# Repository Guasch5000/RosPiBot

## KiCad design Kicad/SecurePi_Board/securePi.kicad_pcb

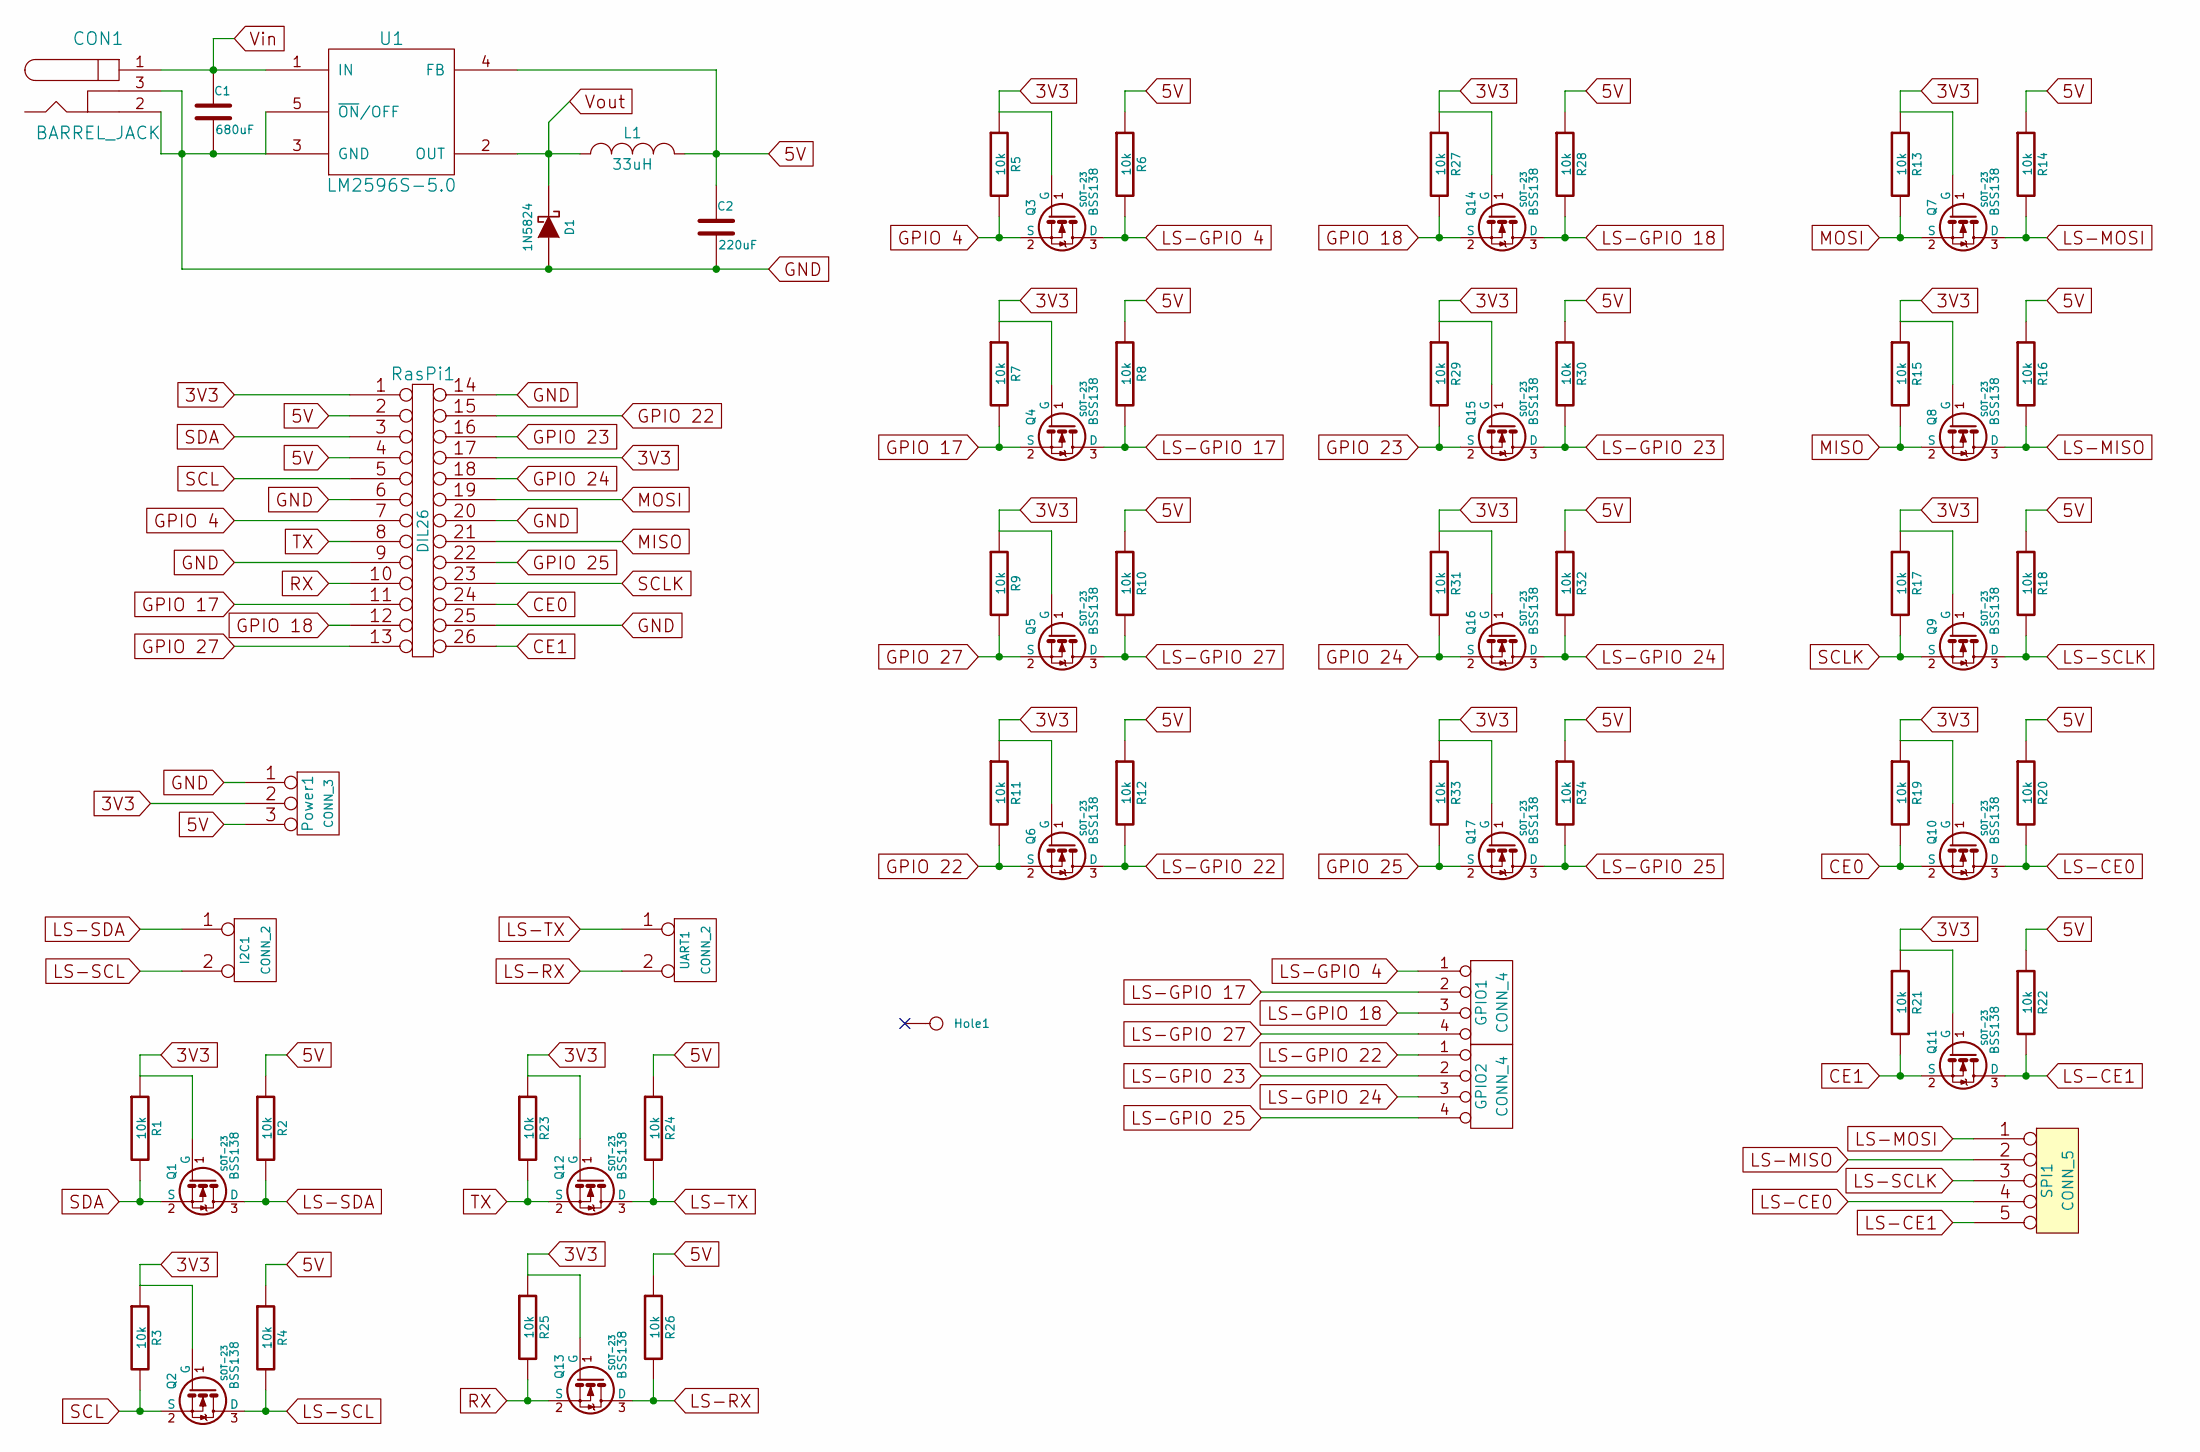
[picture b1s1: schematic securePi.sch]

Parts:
C1: 680uF
C2: 220uF
CON1: BARREL_JACK
D1: 1N5824
GPIO1, GPIO2: CONN_4
Hole1: CONN_1
I2C1: CONN_2
L1: 33uH
Power1: CONN_3
Q1, Q2, Q3, Q4, Q5, Q6, Q7, Q8, Q9, Q10, Q11, Q12, Q13, Q14, Q15, Q16, Q17: BSS138; SOT-23
R1, R2, R3, R4, R5, R6, R7, R8, R9, R10, R11, R12, R13, R14, R15, R16, R17, R18, R19, R20, R21, R22, R23, R24, R25, R26, R27, R28, R29, R30, R31, R32, R33, R34: 10k
RasPi1: DIL26
SPI1: CONN_5
U1: LM2596S-5.0
UART1: CONN_2

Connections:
3V3: Power1.2 (PM), Q1.1 (G), Q2.1 (G), Q3.1 (G), Q4.1 (G), Q5.1 (G), Q6.1 (G), Q7.1 (G), Q8.1 (G), Q9.1 (G), Q10.1 (G), Q11.1 (G), Q12.1 (G), Q13.1 (G), Q14.1 (G), Q15.1 (G), Q16.1 (G), Q17.1 (G), R1.1, R3.1, R5.1, R7.1, R9.1, R11.1, R13.1, R15.1, R17.1, R19.1, R21.1, R23.1, R25.1, R27.1, R29.1, R31.1, R33.1, RasPi1.1, RasPi1.17
5V: C2.1, L1.2, Power1.3, R2.1, R4.1, R6.1, R8.1, R10.1, R12.1, R14.1, R16.1, R18.1, R20.1, R22.1, R24.1, R26.1, R28.1, R30.1, R32.1, R34.1, RasPi1.2, RasPi1.4, U1.4 (FB)
CE0: Q10.2 (S), R19.2, RasPi1.24
CE1: Q11.2 (S), R21.2, RasPi1.26
GND: C1.2, C2.2, CON1.2, CON1.3, D1.1 (A), Power1.1, RasPi1.6, RasPi1.9, RasPi1.14, RasPi1.20, RasPi1.25, U1.3 (GND), U1.5 (~ON~/OFF)
GPIO 4: Q3.2 (S), R5.2, RasPi1.7
GPIO 17: Q4.2 (S), R7.2, RasPi1.11
GPIO 18: Q14.2 (S), R27.2, RasPi1.12
GPIO 22: Q6.2 (S), R11.2, RasPi1.15
GPIO 23: Q15.2 (S), R29.2, RasPi1.16
GPIO 24: Q16.2 (S), R31.2, RasPi1.18
GPIO 25: Q17.2 (S), R33.2, RasPi1.22
GPIO 27: Q5.2 (S), R9.2, RasPi1.13
LS-CE0: Q10.3 (D), R20.2, SPI1.4
LS-CE1: Q11.3 (D), R22.2, SPI1.5
LS-GPIO 4: GPIO1.1, Q3.3 (D), R6.2
LS-GPIO 17: GPIO1.2, Q4.3 (D), R8.2
LS-GPIO 18: GPIO1.3, Q14.3 (D), R28.2
LS-GPIO 22: GPIO2.1, Q6.3 (D), R12.2
LS-GPIO 23: GPIO2.2, Q15.3 (D), R30.2
LS-GPIO 24: GPIO2.3, Q16.3 (D), R32.2
LS-GPIO 25: GPIO2.4, Q17.3 (D), R34.2
LS-GPIO 27: GPIO1.4, Q5.3 (D), R10.2
LS-MISO: Q8.3 (D), R16.2, SPI1.2
LS-MOSI: Q7.3 (D), R14.2, SPI1.1
LS-RX: Q13.3 (D), R26.2, UART1.2 (PM)
LS-SCL: I2C1.2 (PM), Q2.3 (D), R4.2
LS-SCLK: Q9.3 (D), R18.2, SPI1.3
LS-SDA: I2C1.1, Q1.3 (D), R2.2
LS-TX: Q12.3 (D), R24.2, UART1.1
MISO: Q8.2 (S), R15.2, RasPi1.21
MOSI: Q7.2 (S), R13.2, RasPi1.19
RX: Q13.2 (S), R25.2, RasPi1.10
SCL: Q2.2 (S), R3.2, RasPi1.5
SCLK: Q9.2 (S), R17.2, RasPi1.23
SDA: Q1.2 (S), R1.2, RasPi1.3
TX: Q12.2 (S), R23.2, RasPi1.8
Vin: C1.1, CON1.1, U1.1 (IN)
Vout: D1.2 (K), L1.1, U1.2 (OUT)

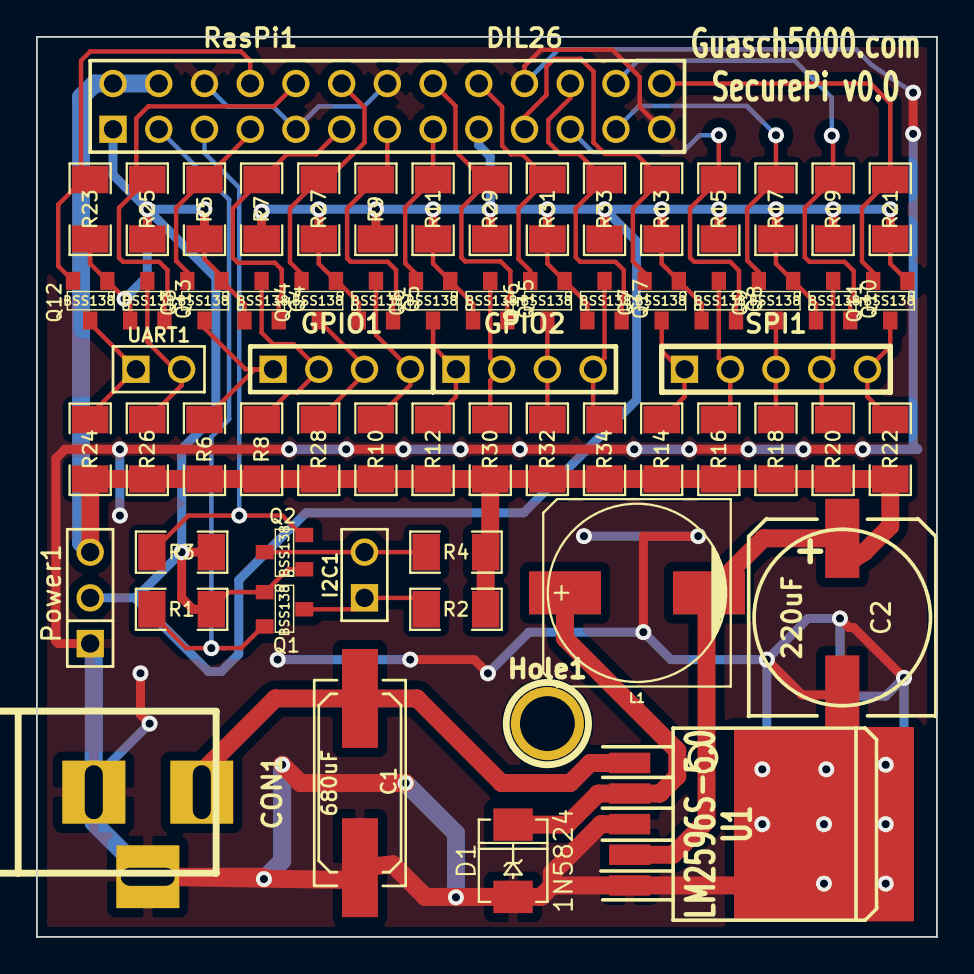
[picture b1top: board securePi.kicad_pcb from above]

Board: 2 copper layers, 50.0 x 50.0 mm, 65 parts (0 on the bottom side), 39 nets.

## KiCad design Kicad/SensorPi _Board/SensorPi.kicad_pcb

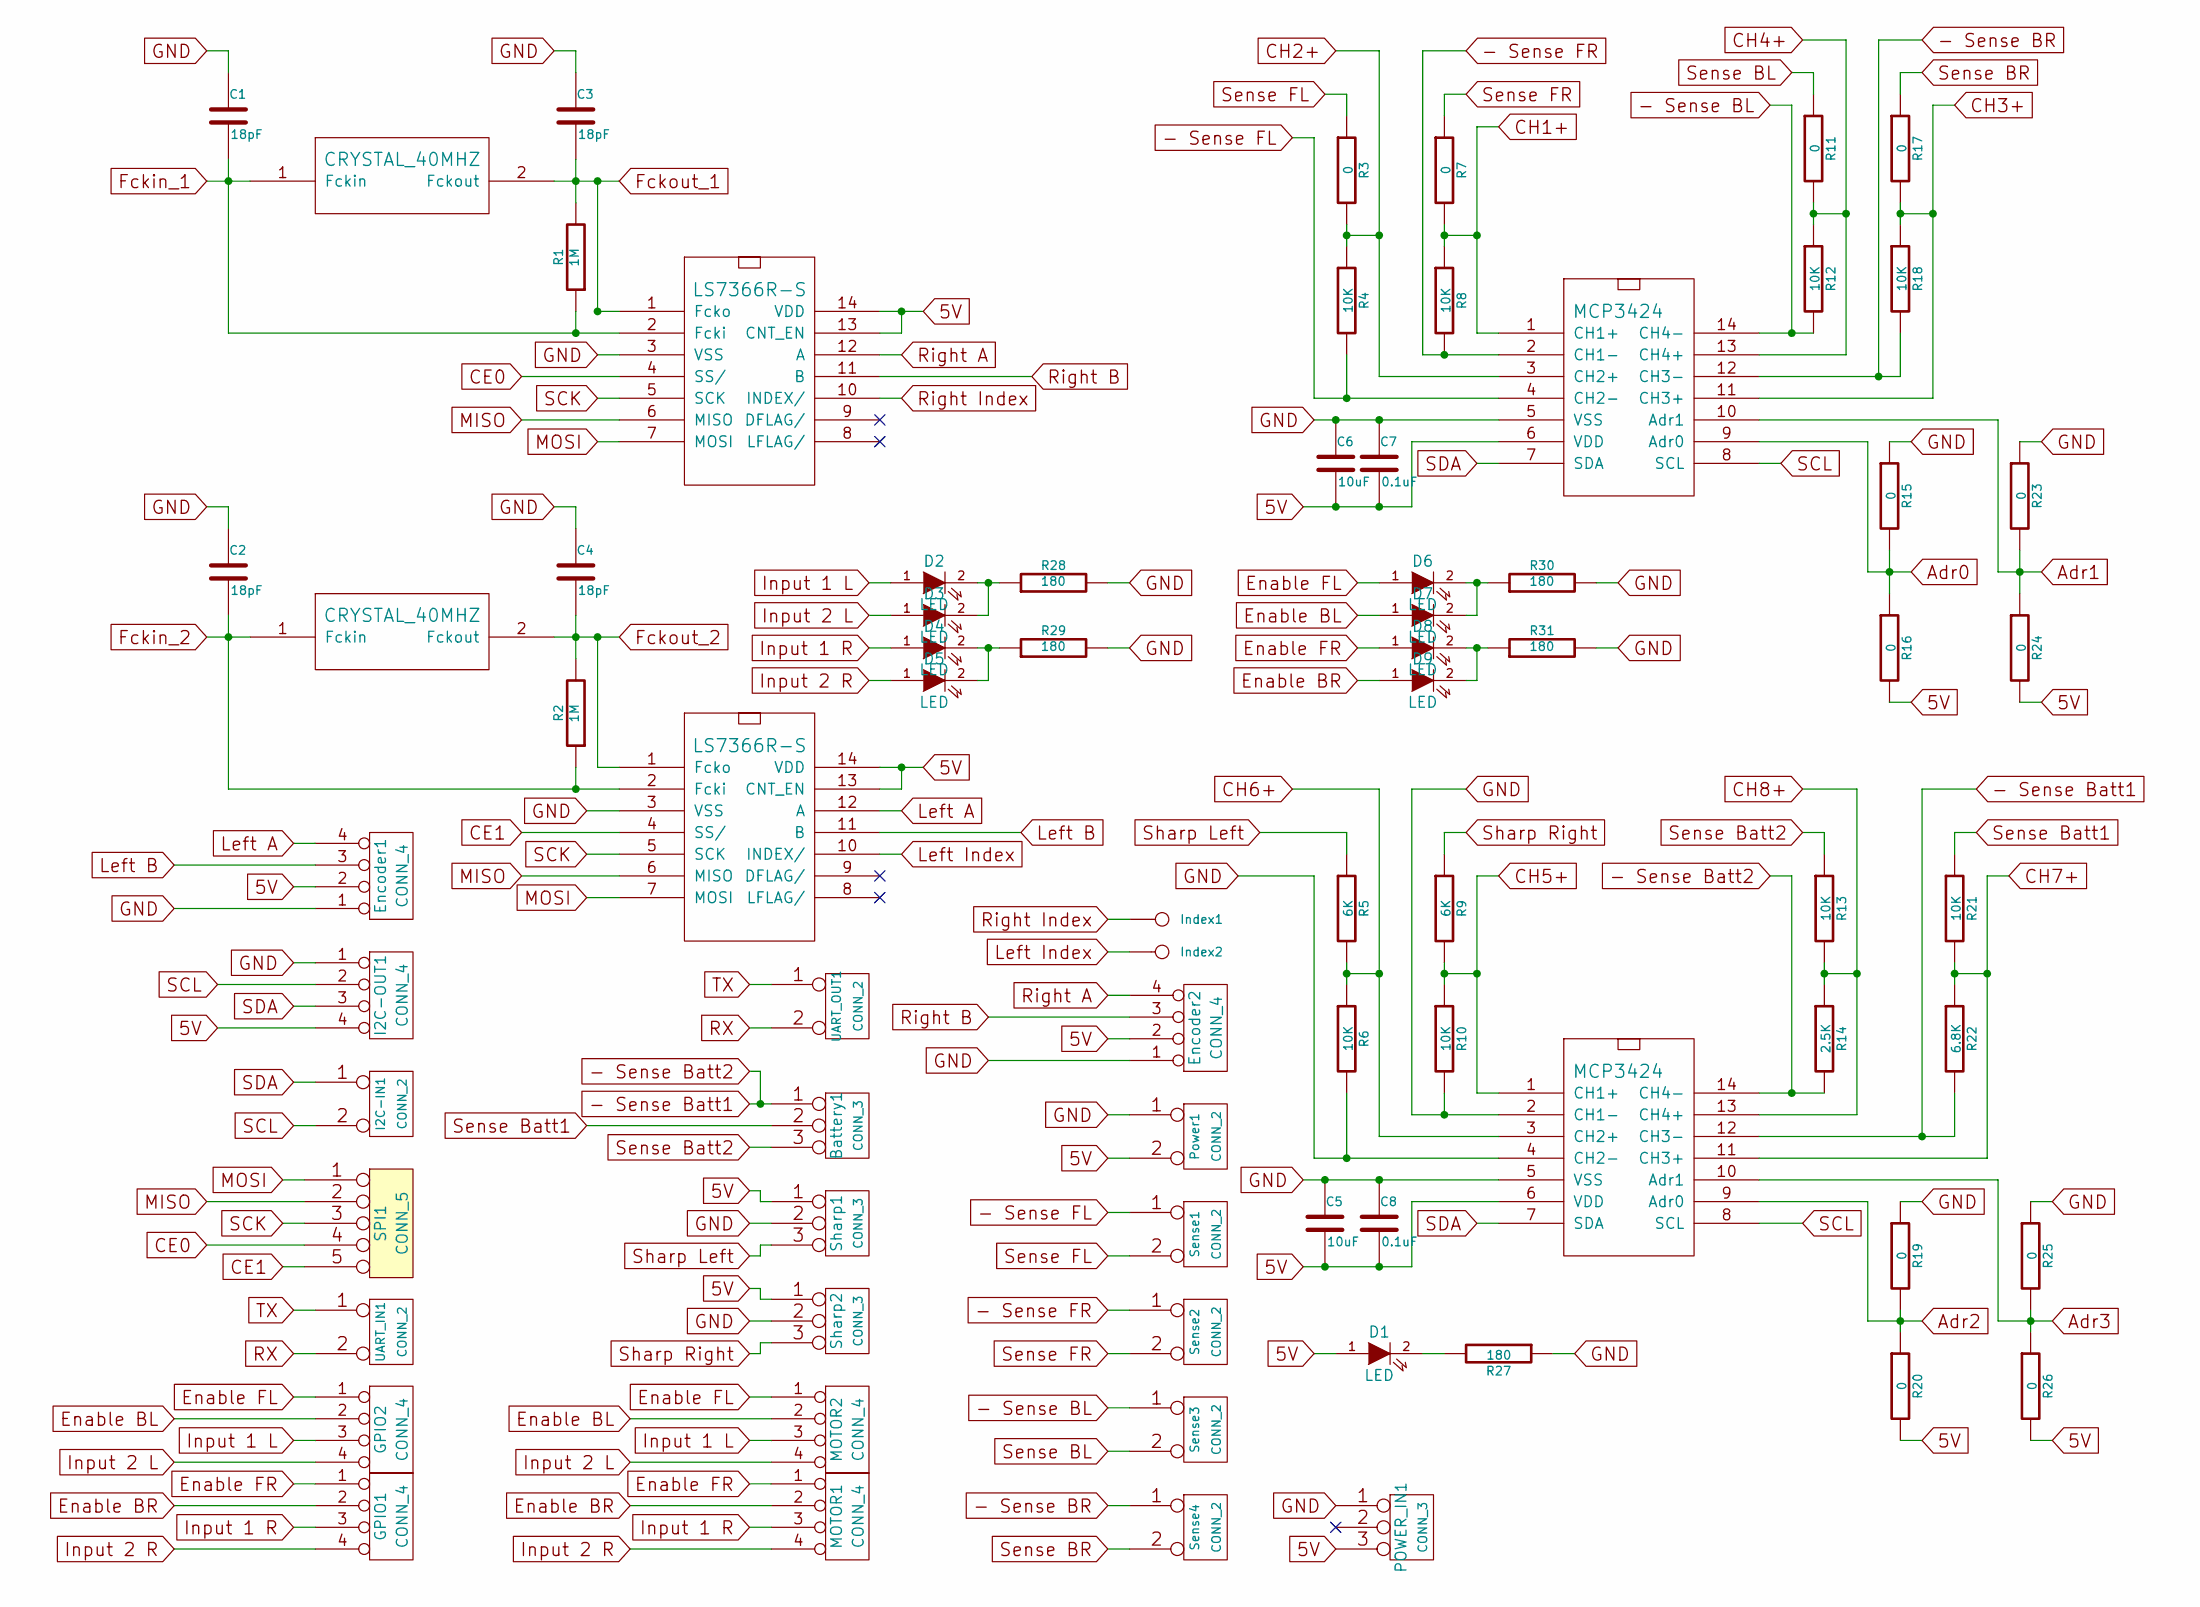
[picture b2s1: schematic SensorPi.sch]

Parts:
Battery1: CONN_3
C1, C2, C3, C4: 18pF
C5, C6: 10uF
C7, C8: 0.1uF
D1, D2, D3, D4, D5, D6, D7, D8, D9: LED
Encoder1, Encoder2: CONN_4
GPIO1, GPIO2: CONN_4
I2C-IN1: CONN_2
I2C-OUT1: CONN_4
Index1, Index2: CONN_1
MOTOR1, MOTOR2: CONN_4
POWER_IN1: CONN_3
Power1: CONN_2
R1, R2: 1M
R3, R7, R11, R15, R16, R17, R19, R20, R23, R24, R25, R26: 0
R4, R6, R8, R10, R12, R13, R18, R21: 10K
R5, R9: 6K
R14: 2.5K
R22: 6.8K
R27, R28, R29, R30, R31: 180
SMD1, SMD2: CRYSTAL_40MHZ
SOIC1, SOIC2: LS7366R-S
SOIC_1, SOIC_2: MCP3424
SPI1: CONN_5
Sense1, Sense2, Sense3, Sense4: CONN_2
Sharp1, Sharp2: CONN_3
UART_IN1: CONN_2
UART_OUT1: CONN_2

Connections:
5V: C5.2, C6.2, C7.2, C8.2, D1.1 (A), Encoder1.2, Encoder2.2, I2C-OUT1.4, POWER_IN1.3, Power1.2 (PM), R16.2, R20.2, R24.2, R26.2, SOIC1.13 (CNT_EN), SOIC1.14 (VDD), SOIC2.13 (CNT_EN), SOIC2.14 (VDD), SOIC_1.6 (VDD), SOIC_2.6 (VDD), Sharp1.1, Sharp2.1; also elsewhere on the board
- Sense BL: R12.2, SOIC_1.14 (CH4-), Sense3.1
- Sense BR: R18.2, SOIC_1.12 (CH3-), Sense4.1
- Sense Batt1: Battery1.1, R14.2, R22.2, SOIC_2.12 (CH3-), SOIC_2.14 (CH4-)
- Sense FL: R4.2, SOIC_1.4 (CH2-), Sense1.1
- Sense FR: R8.2, SOIC_1.2 (CH1-), Sense2.1
Adr0: R15.2, R16.1, SOIC_1.9 (Adr0)
Adr1: R23.2, R24.1, SOIC_1.10 (Adr1)
Adr2: R19.2, R20.1, SOIC_2.9 (Adr0)
Adr3: R25.2, R26.1, SOIC_2.10 (Adr1)
CE0: SOIC1.4 (SS/), SPI1.4
CE1: SOIC2.4 (SS/), SPI1.5
CH1+: R7.2, R8.1, SOIC_1.1 (CH1+)
CH2+: R3.2, R4.1, SOIC_1.3 (CH2+)
CH3+: R17.2, R18.1, SOIC_1.11 (CH3+)
CH4+: R11.2, R12.1, SOIC_1.13 (CH4+)
CH5+: R9.2, R10.1, SOIC_2.1 (CH1+)
CH6+: R5.2, R6.1, SOIC_2.3 (CH2+)
CH7+: R21.2, R22.1, SOIC_2.11 (CH3+)
CH8+: R13.2, R14.1, SOIC_2.13 (CH4+)
Enable BL: D7.1 (A), GPIO2.2, MOTOR2.2
Enable BR: D9.1 (A), GPIO1.2, MOTOR1.2
Enable FL: D6.1 (A), GPIO2.1, MOTOR2.1
Enable FR: D8.1 (A), GPIO1.1, MOTOR1.1
Fckin_1: C1.2, R1.1, SMD1.1 (Fckin), SOIC1.2 (Fcki)
Fckin_2: C2.2, R2.1, SMD2.1 (Fckin), SOIC2.2 (Fcki)
Fckout_1: C3.2, R1.2, SMD1.2 (Fckout), SOIC1.1 (Fcko)
Fckout_2: C4.2, R2.2, SMD2.2 (Fckout), SOIC2.1 (Fcko)
GND: C1.1, C2.1, C3.1, C4.1, C5.1, C6.1, C7.1, C8.1, Encoder1.1, Encoder2.1, I2C-OUT1.1, POWER_IN1.1, Power1.1, R6.2, R10.2, R15.1, R19.1, R23.1, R25.1, R27.1, R28.2, R29.2, R30.2, R31.2, SOIC1.3 (VSS), SOIC2.3 (VSS), SOIC_1.5 (VSS), SOIC_2.2 (CH1-), SOIC_2.4 (CH2-), SOIC_2.5 (VSS), Sharp1.2 (PM), Sharp2.2 (PM); also elsewhere on the board
Input 1 L: D2.1 (A), GPIO2.3, MOTOR2.3
Input 1 R: D4.1 (A), GPIO1.3, MOTOR1.3
Input 2 L: D3.1 (A), GPIO2.4, MOTOR2.4
Input 2 R: D5.1 (A), GPIO1.4, MOTOR1.4
Left A: Encoder1.4, SOIC2.12 (A)
Left B: Encoder1.3, SOIC2.11 (B)
Left Index: Index2.1, SOIC2.10 (INDEX/)
MISO: SOIC1.6 (MISO), SOIC2.6 (MISO), SPI1.2
MOSI: SOIC1.7 (MOSI), SOIC2.7 (MOSI), SPI1.1
unnamed: D4.2 (K), D5.2 (K), R29.1
unnamed: D2.2 (K), D3.2 (K), R28.1
unnamed: D1.2 (K), R27.2
unnamed: D6.2 (K), D7.2 (K), R30.1
unnamed: D8.2 (K), D9.2 (K), R31.1
RX: UART_IN1.2 (PM), UART_OUT1.2 (PM); also elsewhere on the board
Right A: Encoder2.4, SOIC1.12 (A)
Right B: Encoder2.3, SOIC1.11 (B)
Right Index: Index1.1, SOIC1.10 (INDEX/)
SCK: SOIC1.5 (SCK), SOIC2.5 (SCK), SPI1.3
SCL: I2C-IN1.2 (PM), I2C-OUT1.2, SOIC_1.8 (SCL), SOIC_2.8 (SCL); also elsewhere on the board
SDA: I2C-IN1.1, I2C-OUT1.3, SOIC_1.7 (SDA), SOIC_2.7 (SDA); also elsewhere on the board
Sense BL: R11.1, Sense3.2 (PM)
Sense BR: R17.1, Sense4.2 (PM)
Sense Batt1: Battery1.2 (PM), R21.1
Sense Batt2: Battery1.3, R13.1
Sense FL: R3.1, Sense1.2 (PM)
Sense FR: R7.1, Sense2.2 (PM)
Sharp Left: R5.1, Sharp1.3
Sharp Right: R9.1, Sharp2.3
TX: UART_IN1.1, UART_OUT1.1; also elsewhere on the board

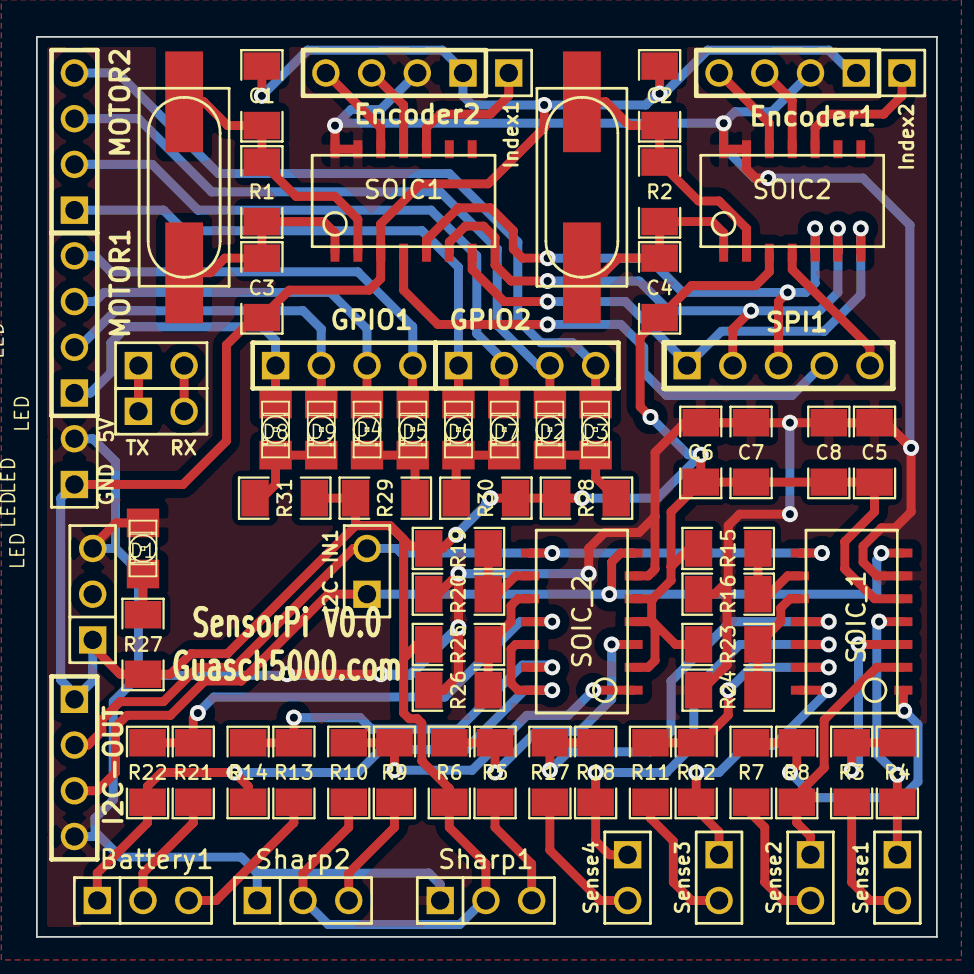
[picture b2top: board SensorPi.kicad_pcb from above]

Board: 2 copper layers, 50.0 x 50.0 mm, 76 parts (0 on the bottom side), 59 nets.

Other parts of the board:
GND  5V: CONN_2; PIN_ARRAY_2X1
I2C-OUT: CONN_4; PIN_ARRAY_4x1
TX  RX: CONN_2; PIN_ARRAY_2X1

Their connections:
5V: GND 5V.2, I2C-OUT.4; also elsewhere on the board
GND: GND 5V.1, I2C-OUT.1; also elsewhere on the board
RX: TX RX.2; also elsewhere on the board
SCL: I2C-OUT.2; also elsewhere on the board
SDA: I2C-OUT.3; also elsewhere on the board
TX: TX RX.1; also elsewhere on the board

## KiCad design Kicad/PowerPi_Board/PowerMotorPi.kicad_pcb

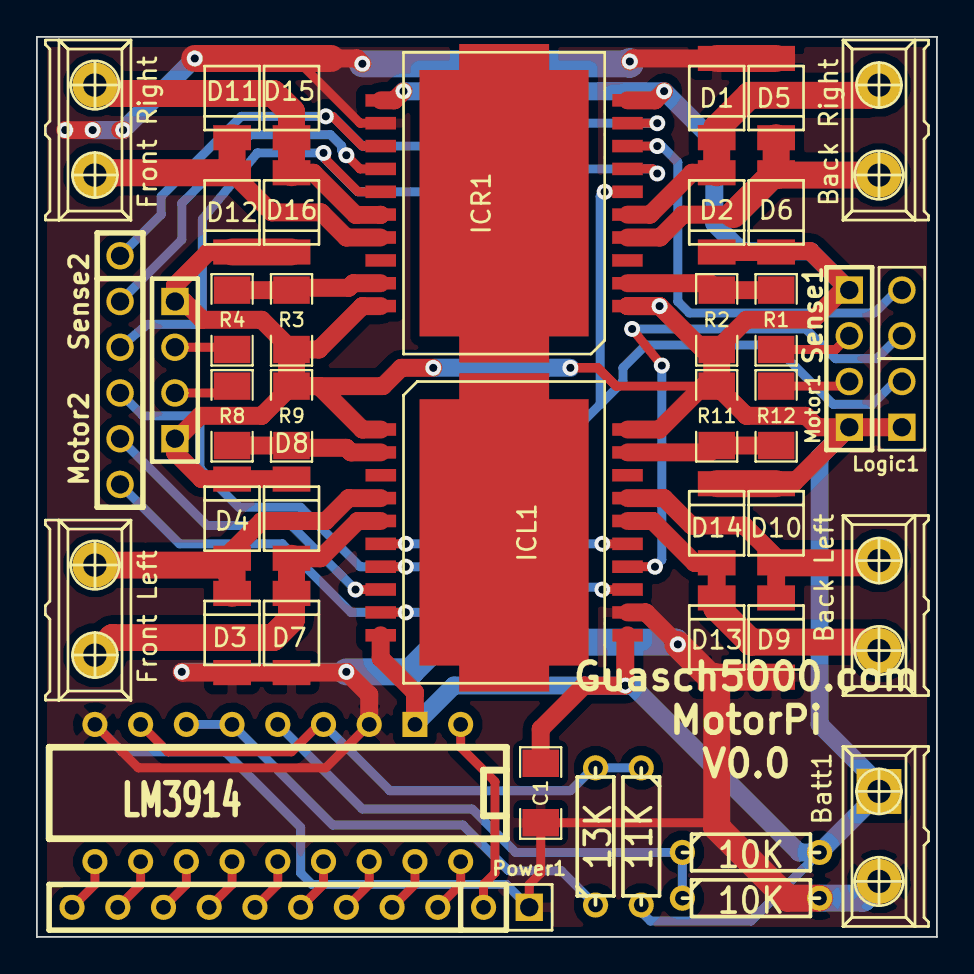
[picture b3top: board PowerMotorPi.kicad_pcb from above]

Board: 2 copper layers, 50.0 x 50.0 mm, 44 parts (0 on the bottom side), 40 nets.

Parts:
Back Left: CONN_2; Block_Terminal_green_2_pins
Back Right: CONN_2; Block_Terminal_green_2_pins
Batt1: CONN_2; Block_Terminal_green_2_pins_Batt
C1: 1uF; SM1206
D1, D2, D3, D4, D5, D6, D7, D8, D9, D10, D11, D12, D13, D14, D15, D16: DIODESCH; SMD_Schottky
DIP1: LM3914; DIP-18__300
Front Left: CONN_2; Block_Terminal_green_2_pins
Front Right: CONN_2; Block_Terminal_green_2_pins
ICL1: L298; L298P
ICR1: L298; L298P
LED1: CONN_10; SIL-10
Logic1: CONN_2; PIN_ARRAY_2X1
Motor1: CONN_2; PIN_ARRAY_2X1
Motor2: CONN_6; PIN_ARRAY-6X1
Power1: CONN_1; PIN_ARRAY_1
R1, R4, R8, R12: 1K; SM1206
R2, R3, R9, R11: 0.5; SM1206
R5, R6: 10K; R3
R7: 11K; R3
R10: 13K; R3
Sense1, Sense2: CONN_4; PIN_ARRAY_4x1

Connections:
5V: ICL1.6, ICR1.6, Logic1.2
GND: Batt1.1, C1.1, D2.1, D4.1, D6.1, D8.1, D10.1, D12.1, D14.1, D16.1, DIP1.2, ICL1.1, ICL1.10, ICL1.11, ICL1.20, ICR1.1, ICR1.10, ICR1.11, ICR1.20, Logic1.1, R2.2, R3.2, R6.2, R7.2, R9.2, R11.2, Sense1.1, Sense1.4, Sense2.1, Sense2.4
IN: DIP1.5, R5.1, R6.1
L Enable A: ICL1.8, Motor2.5
L Enable B: ICL1.14, Motor1.2
L Input 1: ICL1.7, ICL1.15, Motor2.4
L Input 2: ICL1.9, ICL1.13, Motor2.6
L Out 1: D3.1, D4.2, Front Left.2, ICL1.4
L Out 2: D7.1, D8.2, Front Left.1, ICL1.5
L Out 3: Back Left.2, D13.1, D14.2, ICL1.16
L Out 4: Back Left.1, D9.1, D10.2, ICL1.17
L Sense A: ICL1.2, R8.2, R9.1
L Sense ADC A: R8.1, Sense2.2
L Sense ADC B: R12.1, Sense1.3
L Sense B: ICL1.19, R11.1, R12.2
Led 1: DIP1.1, LED1.1
Led 2: DIP1.18, LED1.2
Led 3: DIP1.17, LED1.3
Led 4: DIP1.16, LED1.4
Led 5: DIP1.15, LED1.5
Led 6: DIP1.14, LED1.6
Led 7: DIP1.13, LED1.7
Led 8: DIP1.12, LED1.8
Led 9: DIP1.11, LED1.9
Led 10: DIP1.10, LED1.10
R Enable A: ICR1.8, Motor1.1
R Enable B: ICR1.14, Motor2.2
R Input 1: ICR1.7, ICR1.15, Motor2.3
R Input 2: ICR1.9, ICR1.13, Motor2.1
R Out 1: Back Right.2, D5.1, D6.2, ICR1.4
R Out 2: Back Right.1, D1.1, D2.2, ICR1.5
R Out 3: D15.1, D16.2, Front Right.2, ICR1.16
R Out 4: D11.1, D12.2, Front Right.1, ICR1.17
R Sense A: ICR1.2, R1.2, R2.1
R Sense ADC A: R1.1, Sense1.2
R Sense ADC B: R4.1, Sense2.3
R Sense B: ICR1.19, R3.1, R4.2
R_hi: DIP1.6, DIP1.7, R10.1
R_lo: DIP1.4, DIP1.8, R7.1, R10.2
VSS: Batt1.2, C1.2, D1.2, D3.2, D5.2, D7.2, D9.2, D11.2, D13.2, D15.2, DIP1.3, DIP1.9, ICL1.12, ICR1.12, Power1.1, R5.2

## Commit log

2014-03-10 including all kicad files
2014-03-10 adding folders
2014-03-12 adding LaTex files
2014-03-14 Creating LaTex template
2014-03-14 updating template
2014-03-14 Latex Especification write
2014-03-14 changing Informatica to Software concept
2014-03-14 updating latex
2014-03-17 adding I2C ultrasound sensor comunication
2014-03-18 adding reading with two devices
2014-03-21 web based terminal
2014-03-21 modify KS103 codes
2014-03-24 Changing name to the project
2014-03-24 More specification in latex document
2014-03-24 adding electronics and mechanics specifications
2014-03-24 modifing Specifications and Resume
2014-03-25 changing abstract text and adding Modification part
2014-03-27 Adding battery modifications
2014-03-31 losing time...
2014-04-01 Updating Raspberry Pi description
2014-04-01 Updating wifibot description
2014-04-01 time to coffe! enough Latex
2014-04-01 Quadrature Encoder explanation (after coffee)
2014-04-02 Updating battery decision
2014-04-08 Adding ADC module comunication via I2c
2014-04-30 more latex
2014-05-02 electronic components
2014-05-07 adding regulator descripction
2014-05-07 More Buck description
2014-05-10 Adding more modification in Latex
2014-05-12 More Latexz
2014-05-13 PCB definitions
2014-05-13 Adding MemCached examples
    Used for sahring variable between scripts in python. Also can be used
    for PHP
2014-05-17 Ading Wired connections Latex
2014-05-17 Changing Latex name file
2014-05-18 Adding Mechanical modification in Latex
2014-05-18 Finished assembly chapter
2014-05-18 Adding SolidWorks files
2014-05-18 Adding Data Publisher codes
2014-05-22 Adding Software description in Latex
2014-05-22 Module Description
2014-05-24 Basic programs descriptions, Publishers
2014-05-24 Finished rospibot module description
2014-05-25 ROS Groovy Instalation updated
2014-05-25 Costs defined!
2014-05-25 Added envioremental impact, conclusions, and more
2014-05-26 Adding planification and gantt diagram
2014-05-27 Added bibliography
2014-05-29 Finish Him!
2014-05-29 added front page
2014-06-04 Latex Template
2014-06-04 Revert to 56e05fced
2014-06-04 deleting template
2014-06-16 updating PFC Latex template
